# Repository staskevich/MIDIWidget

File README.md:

MIDIWidget

copyright 2015-2017 John Staskevich

john@codeandcopper.com

This work is licensed under a Creative Commons Attribution 4.0 International License.
http://creativecommons.org/licenses/by/4.0/

HARDWARE:

Eagle 6 board and schematic are in the pcb/ folder. There is also a design for a "programming cradle" that mates the test points on the MIDIWidget with a AVR programmer for ISP.

A public CircuitHub project is available for on-demand manufacturing:
https://circuithub.com/projects/CodeandCopper1/MIDIWidget

FIRMWARE:

See README.txt in Firmware/ and Bootloader/ folders.

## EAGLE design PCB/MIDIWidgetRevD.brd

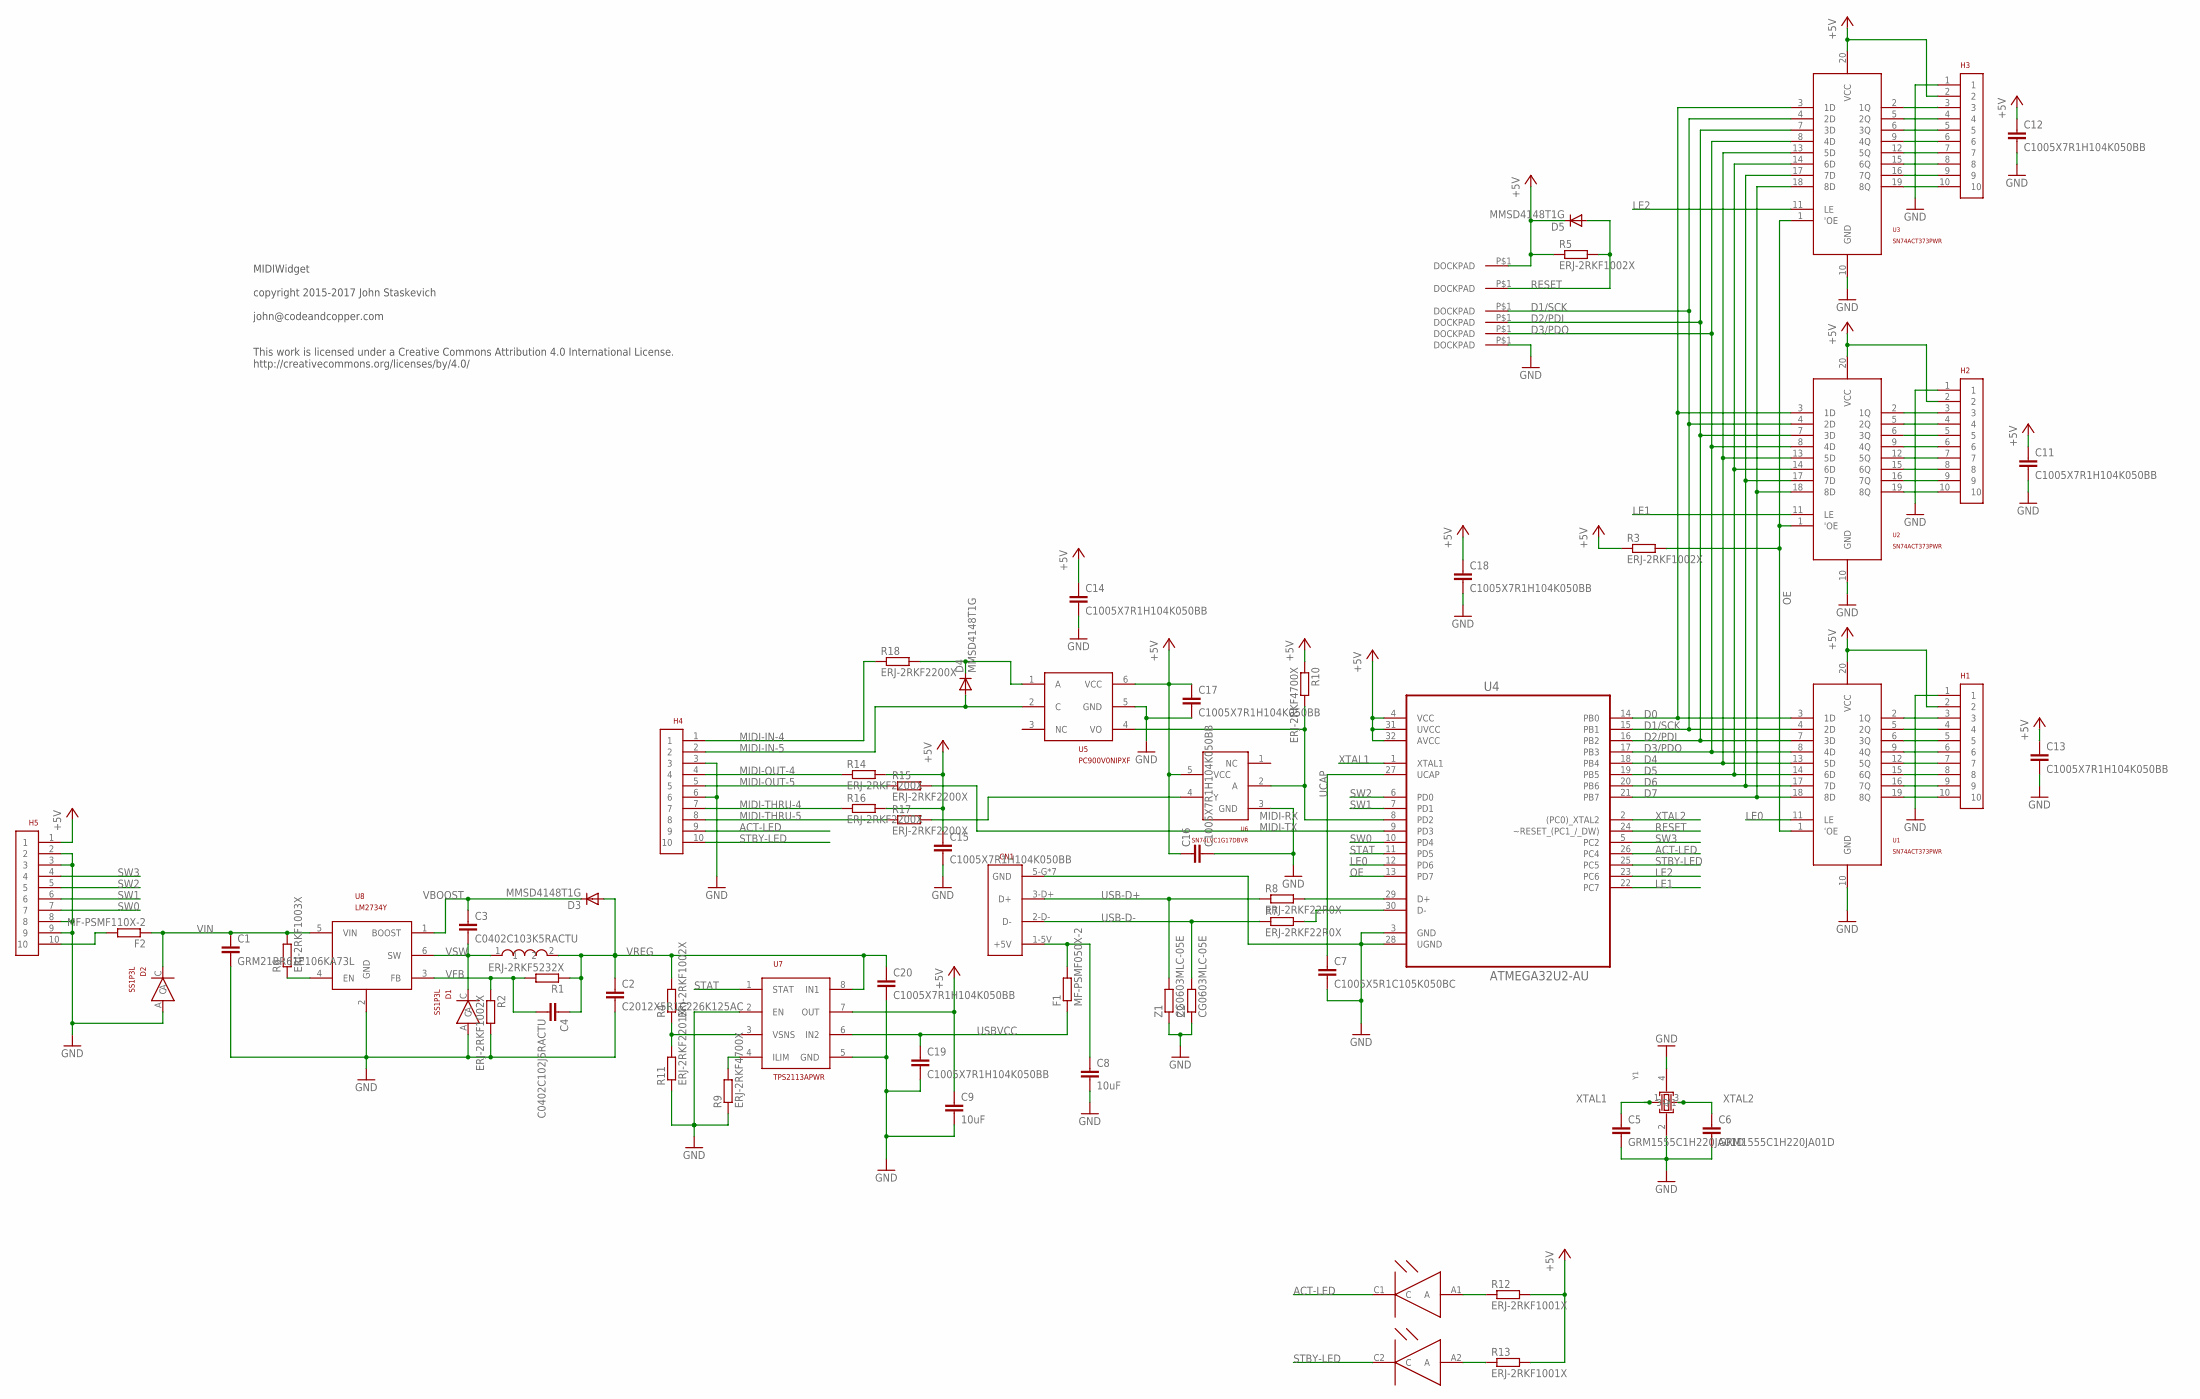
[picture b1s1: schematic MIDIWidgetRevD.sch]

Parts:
C1: GRM21BR61E106KA73L; C0805
C2: C2012X5R1C226K125AC; C0805
C3: C0402C103K5RACTU; C0402
C4: C0402C102J5RACTU; C0402
C5, C6: GRM1555C1H220JA01D; C0402
C7: C1005X5R1C105K050BC; C0402
C8, C9: 10uF; C0805
C11, C12, C13, C14, C15, C16, C17, C18, C19, C20: C1005X7R1H104K050BB; C0402
CN1: 10118192-0001LF; USB-MICRO-B
D1, D2: SS1P3L; DO-220AA(SMP)
D3, D4, D5: MMSD4148T1G; SOD123
DOCK-GND: DOCKPAD; DOCKPAD-ROUND-2.0MM
DOCK-PDI: DOCKPAD; DOCKPAD-ROUND-2.0MM
DOCK-PDO: DOCKPAD; DOCKPAD-ROUND-2.0MM
DOCK-RESET: DOCKPAD; DOCKPAD-ROUND-2.0MM
DOCK-SCK: DOCKPAD; DOCKPAD-ROUND-2.0MM
DOCK-VCC: DOCKPAD; DOCKPAD-ROUND-2.0MM
F1: MF-PSMF050X-2; R0805
F2: MF-PSMF110X-2; R0805
H1, H2, H3, H4, H5: TERMINAL-BLOCK-10POS; TB-2-54-10POS
L1: SLF7055T-220M1R7-3PF; SLF7055
LED: HSMF-C155; LUMEX-1210-DUAL-LED
R1: ERJ-2RKF5232X; R0402
R2, R3, R4, R5: ERJ-2RKF1002X; R0402
R6: ERJ-2RKF1003X; R0402
R7, R8: ERJ-2RKF22R0X; R0402
R9, R10: ERJ-2RKF4700X; R0402
R11: ERJ-2RKF2201X; R0402
R12, R13: ERJ-2RKF1001X; R0402
R14, R15, R16, R17, R18: ERJ-2RKF2200X; R0402
U1, U2, U3: SN74ACT373PWR; TSSOP-20
U4: ATMEGA32U2-AU; QFP80P900X900X120-32N
U5: PC900V0NIPXF; SMT-6
U6: SN74LVC1G17DBVR; SOT23-5-GOOD
U7: TPS2113APWR; TSSOP-8-NAKED
U8: LM2734Y; TSOT-6
Y1: 403C35E16M00000; CRYSTAL-32-25MM
Z1, Z2: CG0603MLC-05E; R0603

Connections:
+5V: C9.1, C11.1, C12.1, C13.1, C14.1, C15.1, C16.1, C17.1, C18.1, D5.C, DOCK-VCC.P$1, H1.2, H2.2, H3.2, H5.1, R3.1, R5.1, R10.1, R12.2, R13.2, R14.2, R16.2, U1.20 (VCC), U2.20 (VCC), U3.20 (VCC), U4.4 (VCC), U4.31 (UVCC), U4.32 (AVCC), U5.6 (VCC), U6.5 (VCC), U7.7 (OUT)
ACT-LED: H4.9, LED.C1 (C), U4.26 (PC4)
D0: U1.3 (1D), U2.3 (1D), U3.3 (1D), U4.14 (PB0)
D1/SCK: DOCK-SCK.P$1, U1.4 (2D), U2.4 (2D), U3.4 (2D), U4.15 (PB1)
D2/PDI: DOCK-PDI.P$1, U1.7 (3D), U2.7 (3D), U3.7 (3D), U4.16 (PB2)
D3/PDO: DOCK-PDO.P$1, U1.8 (4D), U2.8 (4D), U3.8 (4D), U4.17 (PB3)
D4: U1.13 (5D), U2.13 (5D), U3.13 (5D), U4.18 (PB4)
D5: U1.14 (6D), U2.14 (6D), U3.14 (6D), U4.19 (PB5)
D6: U1.17 (7D), U2.17 (7D), U3.17 (7D), U4.20 (PB6)
D7: U1.18 (8D), U2.18 (8D), U3.18 (8D), U4.21 (PB7)
EN: R6.1, U8.4 (EN)
GND: C1.2, C2.2, C5.2, C6.2, C7.2, C8.2, C9.2, C11.2, C12.2, C13.2, C14.2, C15.2, C16.2, C17.2, C18.2, C19.2, C20.2, CN1.5-G (GND), CN1.P$1 (GND), CN1.P$2 (GND), CN1.P$3 (GND), CN1.P$4 (GND), CN1.P$10 (GND), CN1.P$11 (GND), D1.A, D2.A, DOCK-GND.P$1, H1.1, H2.1, H3.1, H4.3, H4.6, H5.2, H5.3, H5.8, H5.9, R2.2, R9.1, R11.1, U1.10 (GND), U2.10 (GND), U3.10 (GND), U4.3 (GND), U4.28 (UGND), U5.5 (GND), U6.3 (GND), U7.2 (EN), U7.5 (GND), U8.2 (GND), Y1.2, Y1.4, Z1.1, Z2.1
ILIM: R9.2, U7.4 (ILIM)
LE0: U1.11 (LE), U4.12 (PD6)
LE1: U2.11 (LE), U4.22 (PC7)
LE2: U3.11 (LE), U4.23 (PC6)
MIDI-IN-4: H4.1, R18.1
MIDI-IN-5: D4.A, H4.2, U5.2 (C)
MIDI-OUT-4: H4.4, R14.1
MIDI-OUT-5: H4.5, R15.1
MIDI-RX: R10.2, U4.8 (PD2), U5.4 (VO), U6.2 (A)
MIDI-THRU-4: H4.7, R16.1
MIDI-THRU-5: H4.8, R17.1
MIDI-TX: R15.2, U4.9 (PD3)
unnamed: H1.10, U1.19 (8Q)
unnamed: H1.9, U1.16 (7Q)
unnamed: H1.8, U1.15 (6Q)
unnamed: H1.7, U1.12 (5Q)
unnamed: H1.6, U1.9 (4Q)
unnamed: H1.5, U1.6 (3Q)
unnamed: H1.4, U1.5 (2Q)
unnamed: H1.3, U1.2 (1Q)
unnamed: H2.3, U2.2 (1Q)
unnamed: H2.4, U2.5 (2Q)
unnamed: H2.5, U2.6 (3Q)
unnamed: H2.6, U2.9 (4Q)
unnamed: H2.7, U2.12 (5Q)
unnamed: H2.8, U2.15 (6Q)
unnamed: H2.9, U2.16 (7Q)
unnamed: H2.10, U2.19 (8Q)
unnamed: H3.9, U3.16 (7Q)
unnamed: H3.10, U3.19 (8Q)
unnamed: H3.8, U3.15 (6Q)
unnamed: H3.7, U3.12 (5Q)
unnamed: H3.6, U3.9 (4Q)
unnamed: H3.5, U3.6 (3Q)
unnamed: H3.4, U3.5 (2Q)
unnamed: H3.3, U3.2 (1Q)
unnamed: D4.C, R18.2, U5.1 (A)
unnamed: LED.A1 (A), R12.1
unnamed: LED.A2 (A), R13.1
unnamed: F2.2, H5.10
unnamed: C8.1, CN1.1-5V (+5V), F1.2
unnamed: R17.2, U6.4 (Y)
OE: R3.2, U1.1 ('OE), U2.1 ('OE), U3.1 ('OE), U4.13 (PD7)
RESET: D5.A, DOCK-RESET.P$1, R5.2, U4.24 (~RESET_(PC1_/_DW))
STAT: U4.11 (PD5), U7.1 (STAT)
STBY-LED: H4.10, LED.C2 (C), U4.25 (PC5)
SW0: H5.7, U4.10 (PD4)
SW1: H5.6, U4.7 (PD1)
SW2: H5.5, U4.6 (PD0)
SW3: H5.4, U4.5 (PC2)
UCAP: C7.1, U4.27 (UCAP)
USB-D+: CN1.3-D+ (D+), R8.1, Z1.2
USB-D+R: R8.2, U4.29 (D+)
USB-D-: CN1.2-D- (D-), R7.1, Z2.2
USB-D-R: R7.2, U4.30 (D-)
USBVCC: C19.1, F1.1, U7.6 (IN2)
VBOOST: C3.1, D3.C, U8.1 (BOOST)
VFB: C4.2, R1.2, R2.1, U8.3 (FB)
VIN: C1.1, D2.C, F2.1, R6.2, U8.5 (VIN)
VREG: C2.1, C4.1, C20.1, D3.A, L1.2, R1.1, R4.2, U7.8 (IN1)
VSNS: R4.1, R11.2, U7.3 (VSNS)
VSW: C3.2, D1.C, L1.1, U8.6 (SW)
XTAL1: C5.1, U4.1 (XTAL1), Y1.1
XTAL2: C6.1, U4.2 ((PC0)_XTAL2), Y1.3

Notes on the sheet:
MIDIWidget copyright 2015-2017 John Staskevich john@codeandcopper.com This work is licensed under a Creative Commons Attribution 4.0 International License. http://creativecommons.org/licenses/by/4.0/

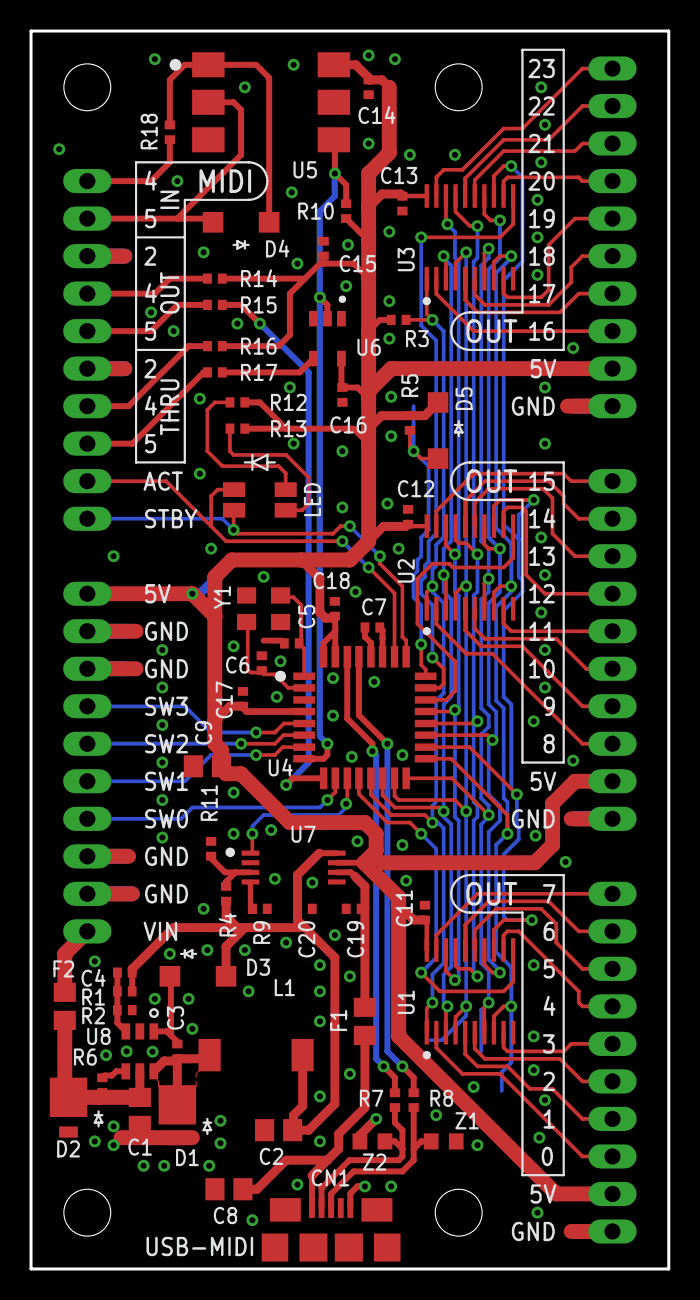
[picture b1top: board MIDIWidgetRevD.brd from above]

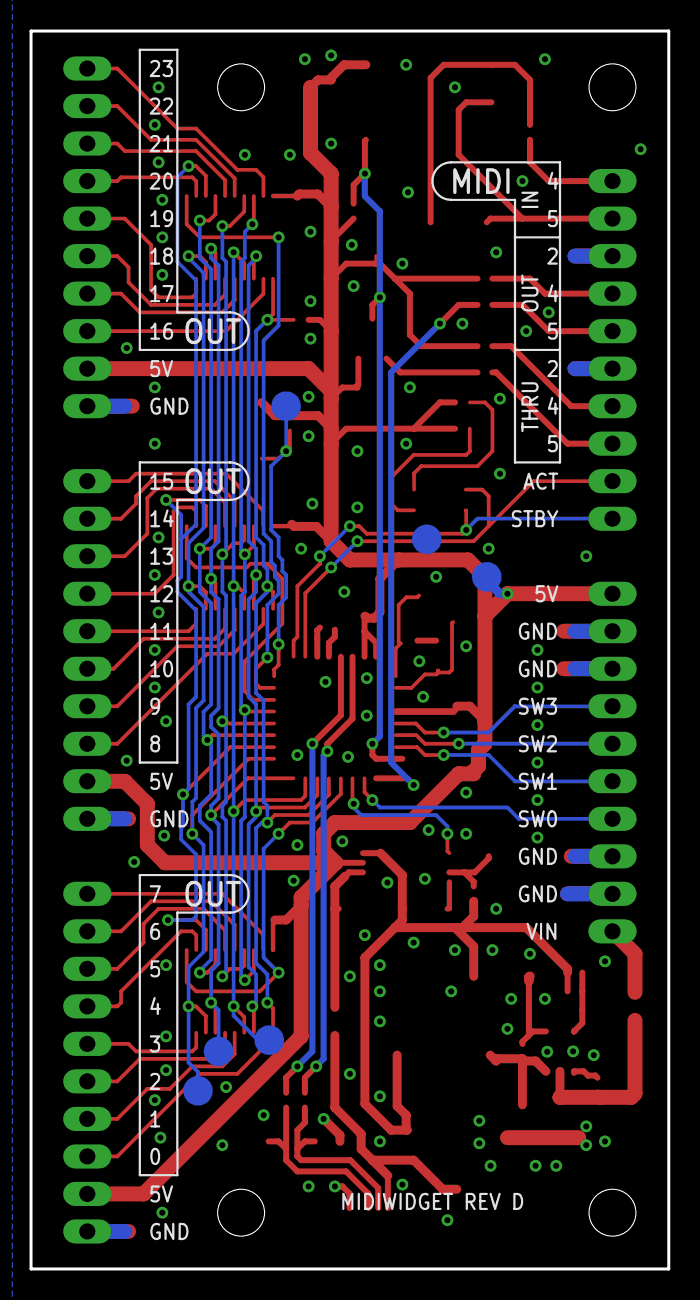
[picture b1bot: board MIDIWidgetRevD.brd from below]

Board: 2 copper layers, 43.2 x 83.8 mm, 69 parts (6 on the bottom side), 76 nets.

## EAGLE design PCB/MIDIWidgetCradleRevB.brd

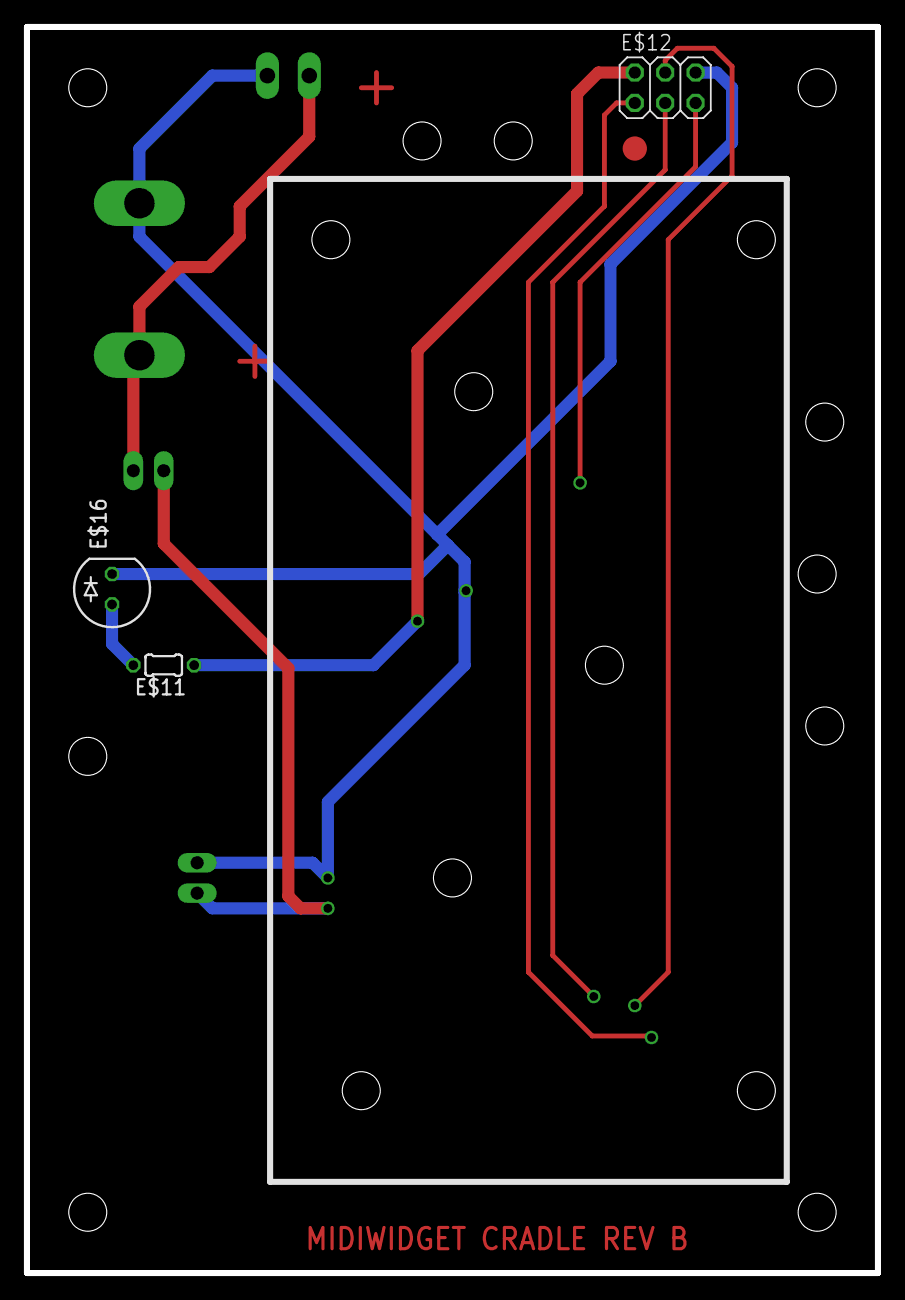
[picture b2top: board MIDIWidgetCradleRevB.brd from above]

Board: 2 copper layers, 71.1 x 104.1 mm, 15 parts (0 on the bottom side), 9 nets.

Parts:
E$1: STUD9V
E$2: TERMINAL-BLOCK-3-5-2POS
E$3, E$4, E$5, E$6, E$7, E$8, E$9, E$10: SPRING-CONTACT-025
E$11: 0204/5
E$12: 2X03
E$13, E$15: TB-2-54-2POS
E$16: LED5MM

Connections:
GND: E$1.P$2, E$2.P$1, E$4.P$1, E$9.P$1, E$12.6, E$13.P$3, E$16.K
ICSPCLK: E$5.P$1, E$12.3
ICSPDAT: E$6.P$1, E$12.1
S$2: E$3.P$1, E$12.5
S$8: E$11.2, E$16.A
VDD: E$8.P$1, E$11.1, E$12.2
VIN: E$1.P$1, E$2.P$2, E$15.P$1
VINRECT: E$10.P$1, E$13.P$1, E$15.P$3
VPP: E$7.P$1, E$12.4

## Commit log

2015-06-01 added application firmware
2015-06-01 added bootloader
2015-06-01 added PCB design
2015-06-01 added configurator
2017-07-26 PCB Rev D
2017-07-26 added cradle PCB for ISP
2018-08-27 added Configurator Mac/Windows executables
